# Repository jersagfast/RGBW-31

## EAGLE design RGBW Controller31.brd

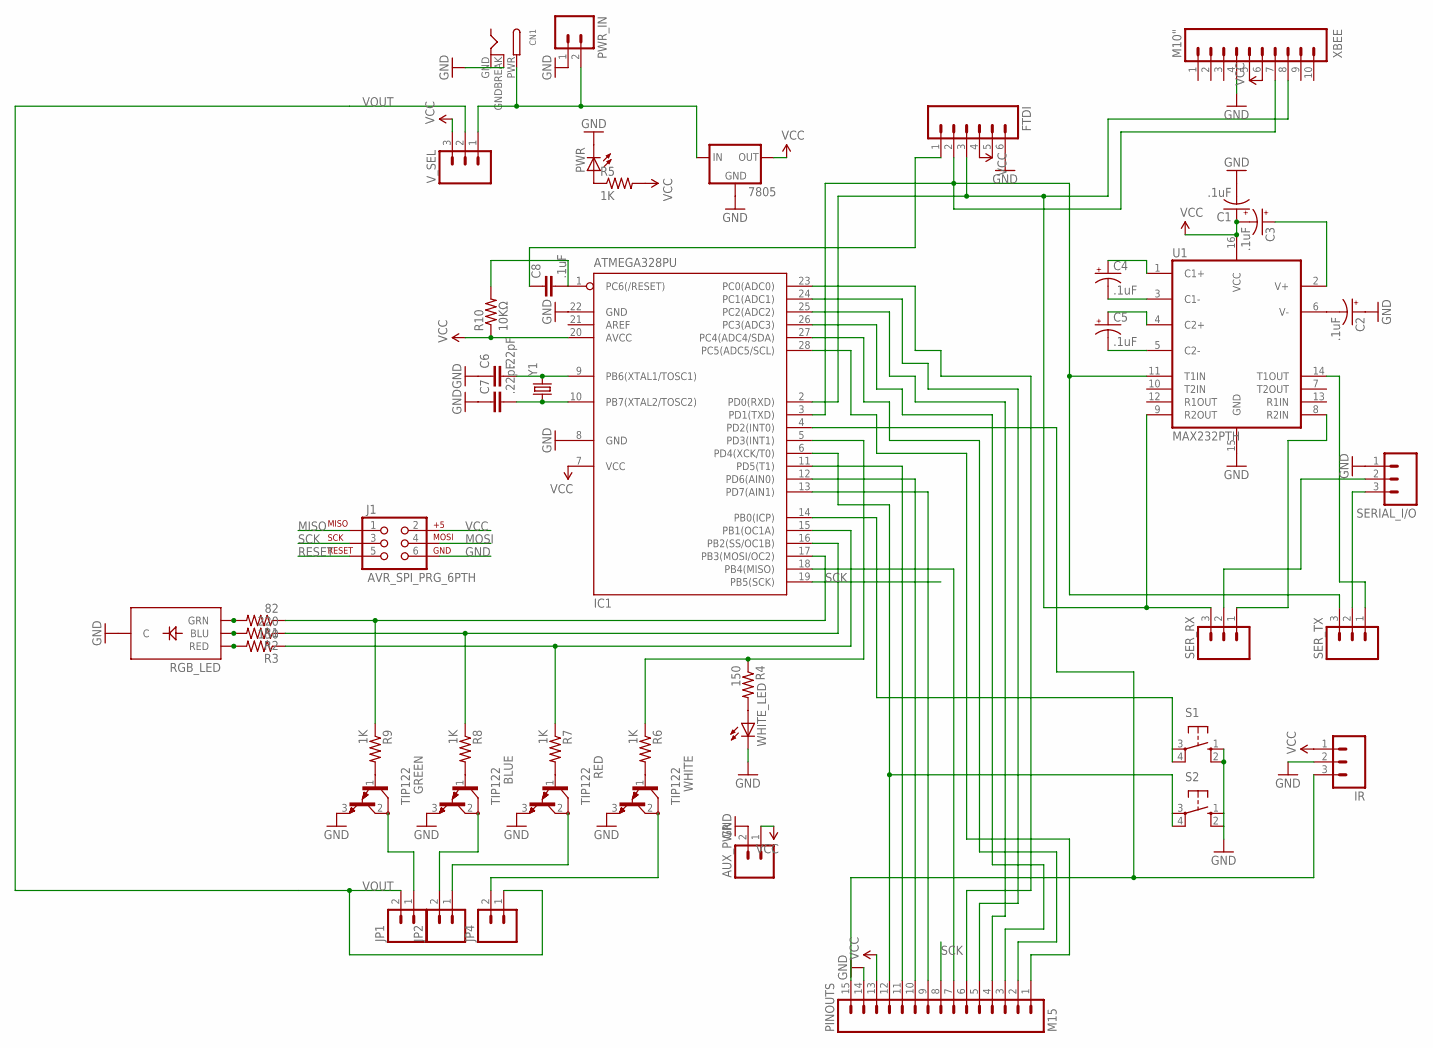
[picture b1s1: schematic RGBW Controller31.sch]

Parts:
7805: V_REG_78XXSIDE; 78XXL
AUX_PWR: M02PTH; 1X02
BLUE: TIP122; TO220
C1, C2, C3, C4, C5: .1uF; CPOL-RADIAL-100UF-25V
C6, C7: .22pF; CAP-PTH-SMALL
C8: .1uF; CAP-PTH-SMALL-KIT
CN1: DCBARRELPTH; DCJACK_2MM_PTH
FTDI: M06SIP; 1X06
GREEN: TIP122; TO220
IC1: ATMEGA328PU; DIL28-3
IR: M03PTH; 1X03
J1: AVR_SPI_PRG_6PTH; 2X3
JP1, JP2, JP4: M025MM; SCREWTERMINAL-5MM-2
PINOUTS: M15; 1X15
PWR: LED5MM
PWR_IN: M025MM; SCREWTERMINAL-5MM-2
R1: 82; AXIAL-0.4
R2: 220; AXIAL-0.4
R3, R4: 150; AXIAL-0.4
R5, R6, R7, R8, R9: 1K; AXIAL-0.4
R10: 10KΩ; AXIAL-0.4
RED: TIP122; TO220
RGB_LED: LED-TRICOLOR-THROUGHHOLE
S1, S2: 10-XX; B3F-10XX
SERIAL_I/O: M03SCREW; SCREWTERMINAL-3.5MM-3
SER_RX: M03PTH; 1X03
SER_TX: M03PTH; 1X03
U1: MAX232PTH; DIL16
V_SEL: M03PTH; 1X03
WHITE: TIP122; TO220
WHITE_LED: LED5MM
XBEE: M10"; 1X10
Y1: CRYSTALHC49US; HC49US

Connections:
GND: 7805.GND, AUX_PWR.2, BLUE.3 (E), C1.2 (-), C2.1 (+), C6.1, C7.1, CN1.GND, CN1.GNDBREAK, FTDI.6, GREEN.3 (E), IC1.8 (GND), IC1.22 (GND), IR.2, J1.6, PINOUTS.14, PWR.K (C), PWR_IN.1, RED.3 (E), RGB_LED.GND (C), S1.1 (S), S1.2 (S1), S2.1 (S), S2.2 (S1), SERIAL_I/O.1, U1.15 (GND), WHITE.3 (E), WHITE_LED.K (C), XBEE.4
MISO: IC1.18 (PB4(MISO)), J1.1, PINOUTS.7
MOSI: IC1.17 (PB3(MOSI/OC2)), J1.4, R1.P$1 (1), R9.P$1 (1)
unnamed: R1.P$2 (2), RGB_LED.GRN
unnamed: R2.P$2 (2), RGB_LED.BLU
unnamed: R3.P$2 (2), RGB_LED.RED
unnamed: R4.P$2 (2), WHITE_LED.A
unnamed: PWR.A, R5.P$1 (1)
unnamed: C5.1 (+), U1.4 (C2+)
unnamed: C4.2 (-), U1.3 (C1-)
unnamed: C4.1 (+), U1.1 (C1+)
unnamed: C5.2 (-), U1.5 (C2-)
unnamed: C3.1 (+), U1.2 (V+)
unnamed: C2.2 (-), U1.6 (V-)
unnamed: IC1.5 (PD3(INT1)), R4.P$1 (1), R6.P$1 (1)
unnamed: IC1.15 (PB1(OC1A)), R3.P$1 (1), R7.P$1 (1)
unnamed: IC1.16 (PB2(SS/OC1B)), R2.P$1 (1), R8.P$1 (1)
unnamed: C6.2, IC1.9 (PB6(XTAL1/TOSC1)), Y1.2
unnamed: C7.2, IC1.10 (PB7(XTAL2/TOSC2)), Y1.1
unnamed: IC1.4 (PD2(INT0)), IR.3, PINOUTS.15
unnamed: 7805.IN, CN1.PWR, PWR_IN.2, V_SEL.1
unnamed: GREEN.2 (C), JP1.1
unnamed: BLUE.2 (C), JP2.2
unnamed: JP2.1, RED.2 (C)
unnamed: JP4.2, WHITE.2 (C)
unnamed: IC1.14 (PB0(ICP)), S1.3, S1.4 (P1)
unnamed: C8.1, FTDI.1
unnamed: FTDI.2, IC1.3 (PD1(TXD)), SER_TX.3, U1.11 (T1IN), XBEE.7
unnamed: FTDI.3, IC1.2 (PD0(RXD)), SER_RX.3, U1.9 (R2OUT), XBEE.8
unnamed: IC1.13 (PD7(AIN1)), PINOUTS.9
unnamed: IC1.12 (PD6(AIN0)), PINOUTS.10
unnamed: IC1.11 (PD5(T1)), PINOUTS.11
unnamed: IC1.26 (PC3(ADC3)), PINOUTS.3
unnamed: IC1.27 (PC4(ADC4/SDA)), PINOUTS.2
unnamed: IC1.28 (PC5(ADC5/SCL)), PINOUTS.1
unnamed: IC1.6 (PD4(XCK/T0)), PINOUTS.12, S2.3, S2.4 (P1)
unnamed: IC1.25 (PC2(ADC2)), PINOUTS.4
unnamed: IC1.24 (PC1(ADC1)), PINOUTS.5
unnamed: IC1.23 (PC0(ADC0)), PINOUTS.6
unnamed: SERIAL_I/O.3, SER_TX.2
unnamed: SERIAL_I/O.2, SER_RX.2
unnamed: SER_TX.1, U1.14 (T1OUT)
unnamed: SER_RX.1, U1.8 (R2IN)
unnamed: R7.P$2 (2), RED.1 (B)
unnamed: BLUE.1 (B), R8.P$2 (2)
unnamed: GREEN.1 (B), R9.P$2 (2)
unnamed: R6.P$2 (2), WHITE.1 (B)
RESET: C8.2, IC1.1 (PC6(/RESET)), J1.5, R10.P$2 (2)
SCK: IC1.19 (PB5(SCK)), J1.3, PINOUTS.8
VCC: 7805.OUT, AUX_PWR.1, C1.1 (+), C3.2 (-), FTDI.4, IC1.7 (VCC), IC1.20 (AVCC), IR.1, J1.2, PINOUTS.13, R5.P$2 (2), R10.P$1 (1), U1.16 (VCC), V_SEL.3, XBEE.6
VOUT: JP1.2, JP4.1, V_SEL.2

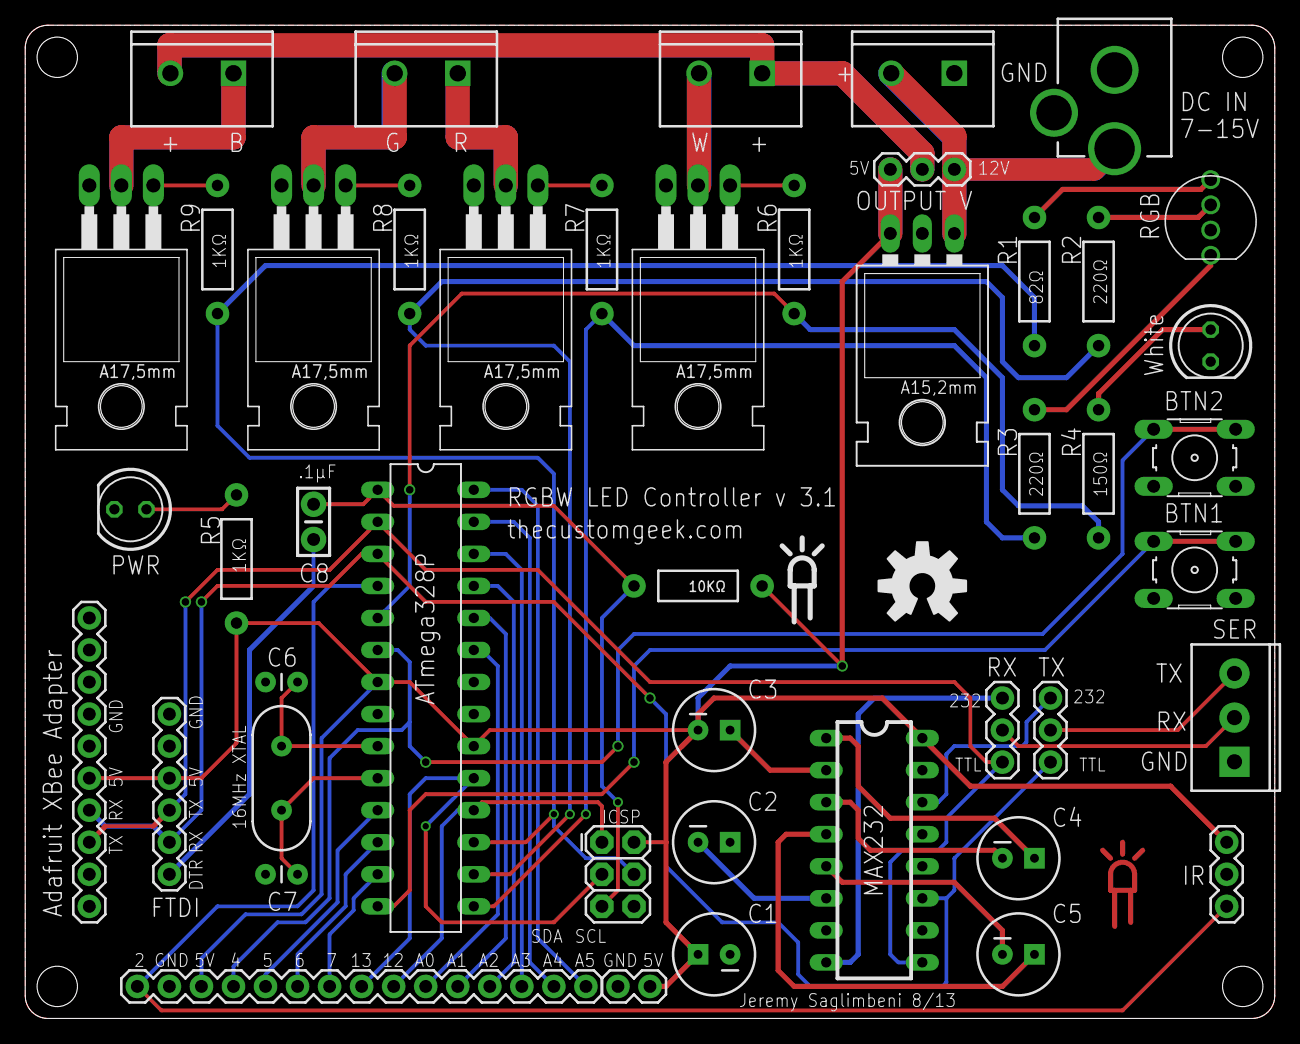
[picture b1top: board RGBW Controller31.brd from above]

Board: 2 copper layers, 99.1 x 78.7 mm, 48 parts (1 on the bottom side), 51 nets.

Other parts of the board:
U$1, U$2: OSHW-LOGO-L

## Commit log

2013-12-28 Fixed IR
